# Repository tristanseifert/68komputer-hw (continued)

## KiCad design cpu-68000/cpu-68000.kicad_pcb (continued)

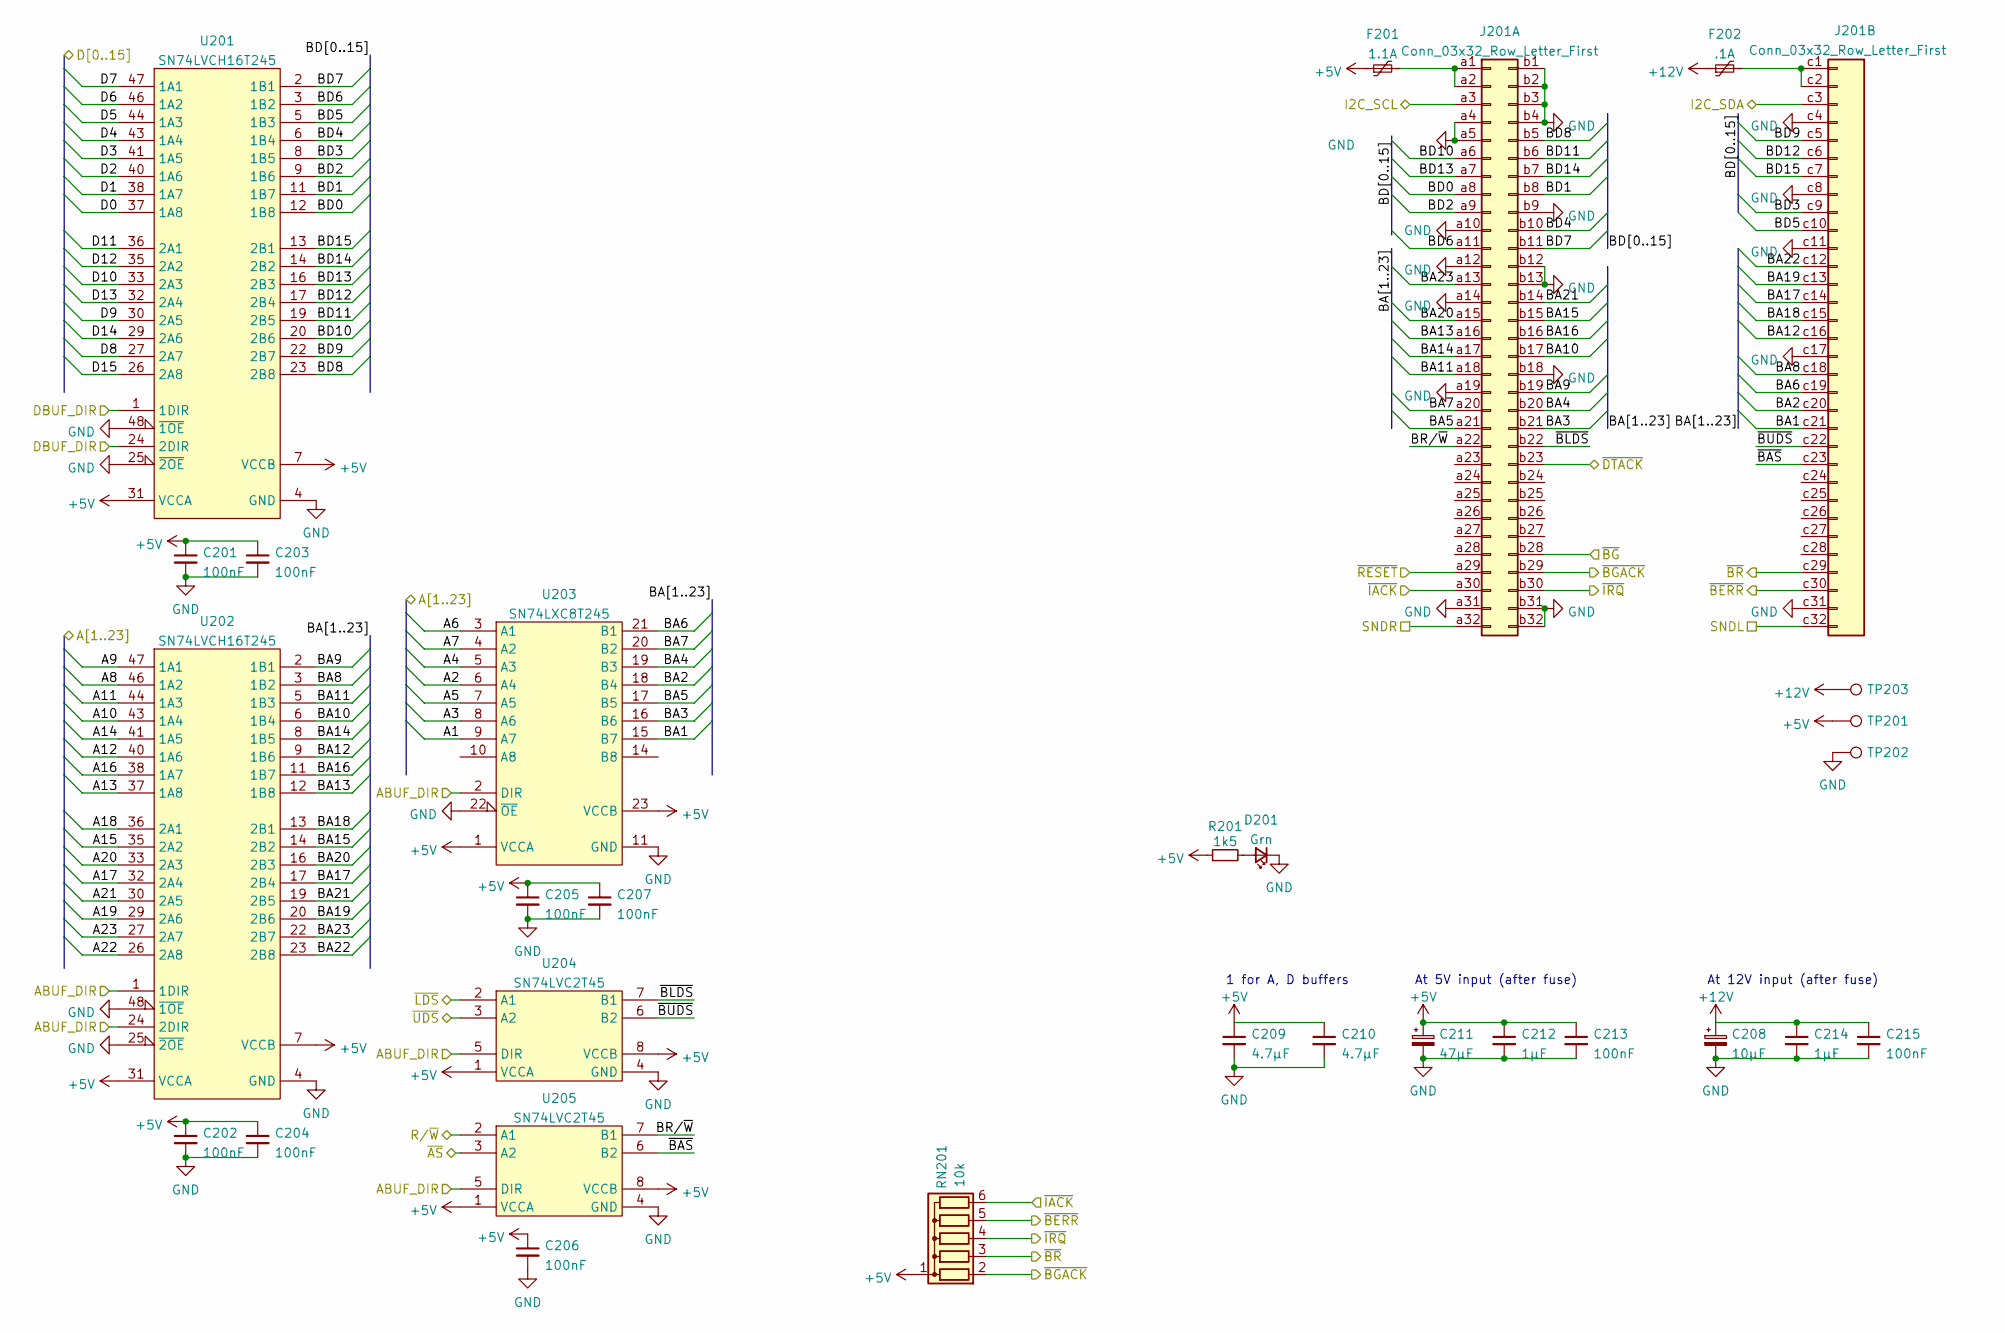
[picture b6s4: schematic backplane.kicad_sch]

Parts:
C201, C202, C203, C204, C205, C206, C207, C213, C215: 100nF; C_0805_2012Metric
C208: 10µF; CP_EIA-3528-21_Kemet-B; MPN TAJB106K025SNJ
C209, C210: 4.7µF; C_0805_2012Metric
C211: 47µF; CP_Radial_D6.3mm_P2.50mm; MPN A750EK476M1EAAE040
C212, C214: 1µF; C_0805_2012Metric
D201: Grn; H100Cxx; MPN H100CGD
F201: 1.1A; Fuse_Bourns_MF-SM_7.98x5.44mm; MPN MF-SM100/33-2
F202: .1A; Fuse_Littelfuse-NANO2-451_453; MPN NANOSMDC010F-2
J201: Conn_03x32_Row_Letter_First; DIN41612_R_3x32_Male_Horizontal_THT
R201: 1k5; R_0805_2012Metric
RN201: 10k; R_Array_SIP6; MPN 4606X-101-103LF
TP201, TP203: TestPoint; TestPoint_Loop_D2.60mm_Drill1.4mm_Beaded; MPN 534-5000
TP202: TestPoint; TestPoint_Loop_D2.60mm_Drill1.4mm_Beaded; MPN 534-5001
U201, U202: SN74LVCH16T245; TSSOP-48_6.1x12.5mm_P0.5mm
U203: SN74LXC8T245; TSSOP-24_4.4x7.8mm_P0.65mm
U204, U205: SN74LVC2T45; VSSOP-8_2.3x2mm_P0.5mm

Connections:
+5V: C201.1, C202.1, C203.1, C204.1, C205.1, C206.1, C207.1, C209.1, C210.1, C211.1, C212.1, C213.1, F201.1, R201.1, RN201.1 (common), TP201.1, U201.7 (VCCB), U201.18 (VCCB), U201.31 (VCCA), U201.42 (VCCA), U202.7 (VCCB), U202.18 (VCCB), U202.31 (VCCA), U202.42 (VCCA), U203.1 (VCCA), U203.23 (VCCB), U203.24 (VCCB), U204.1 (VCCA), U204.8 (VCCB), U205.1 (VCCA), U205.8 (VCCB); also elsewhere on the board
+12V: C208.1, C214.1, C215.1, F202.1, TP203.1; also elsewhere on the board
/A1: U203.9 (A7); also elsewhere on the board
/A2: U203.6 (A4); also elsewhere on the board
/A3: U203.8 (A6); also elsewhere on the board
/A4: U203.5 (A3); also elsewhere on the board
/A5: U203.7 (A5); also elsewhere on the board
/A6: U203.3 (A1); also elsewhere on the board
/A7: U203.4 (A2); also elsewhere on the board
/A8: U202.46 (1A2); also elsewhere on the board
/A9: U202.47 (1A1); also elsewhere on the board
/A10: U202.43 (1A4); also elsewhere on the board
/A11: U202.44 (1A3); also elsewhere on the board
/A12: U202.40 (1A6); also elsewhere on the board
/A13: U202.37 (1A8); also elsewhere on the board
/A14: U202.41 (1A5); also elsewhere on the board
/A15: U202.35 (2A2); also elsewhere on the board
/A16: U202.38 (1A7); also elsewhere on the board
/A17: U202.32 (2A4); also elsewhere on the board
/A18: U202.36 (2A1); also elsewhere on the board
/A19: U202.29 (2A6); also elsewhere on the board
/A20: U202.33 (2A3); also elsewhere on the board
/A21: U202.30 (2A5); also elsewhere on the board
/A22: U202.26 (2A8); also elsewhere on the board
/A23: U202.27 (2A7); also elsewhere on the board
/ABUF_DIR: U202.1 (1DIR), U202.24 (2DIR), U203.2 (DIR), U204.5 (DIR), U205.5 (DIR); also elsewhere on the board
/Backplane Connection/BA1: J201.c21, U203.15 (B7)
/Backplane Connection/BA2: J201.c20, U203.18 (B4)
/Backplane Connection/BA3: J201.b21, U203.16 (B6)
/Backplane Connection/BA4: J201.b20, U203.19 (B3)
/Backplane Connection/BA5: J201.a21, U203.17 (B5)
/Backplane Connection/BA6: J201.c19, U203.21 (B1)
/Backplane Connection/BA7: J201.a20, U203.20 (B2)
/Backplane Connection/BA8: J201.c18, U202.3 (1B2)
/Backplane Connection/BA9: J201.b19, U202.2 (1B1)
/Backplane Connection/BA10: J201.b17, U202.6 (1B4)
/Backplane Connection/BA11: J201.a18, U202.5 (1B3)
/Backplane Connection/BA12: J201.c16, U202.9 (1B6)
/Backplane Connection/BA13: J201.a16, U202.12 (1B8)
/Backplane Connection/BA14: J201.a17, U202.8 (1B5)
/Backplane Connection/BA15: J201.b15, U202.14 (2B2)
/Backplane Connection/BA16: J201.b16, U202.11 (1B7)
/Backplane Connection/BA17: J201.c14, U202.17 (2B4)
/Backplane Connection/BA18: J201.c15, U202.13 (2B1)
/Backplane Connection/BA19: J201.c13, U202.20 (2B6)
/Backplane Connection/BA20: J201.a15, U202.16 (2B3)
/Backplane Connection/BA21: J201.b14, U202.19 (2B5)
/Backplane Connection/BA22: J201.c12, U202.23 (2B8)
/Backplane Connection/BA23: J201.a13, U202.22 (2B7)
/Backplane Connection/BD0: J201.a8, U201.12 (1B8)
/Backplane Connection/BD1: J201.b8, U201.11 (1B7)
/Backplane Connection/BD2: J201.a9, U201.9 (1B6)
/Backplane Connection/BD3: J201.c9, U201.8 (1B5)
/Backplane Connection/BD4: J201.b10, U201.6 (1B4)
/Backplane Connection/BD5: J201.c10, U201.5 (1B3)
/Backplane Connection/BD6: J201.a11, U201.3 (1B2)
/Backplane Connection/BD7: J201.b11, U201.2 (1B1)
/Backplane Connection/BD8: J201.b5, U201.23 (2B8)
/Backplane Connection/BD9: J201.c5, U201.22 (2B7)
/Backplane Connection/BD10: J201.a6, U201.20 (2B6)
/Backplane Connection/BD11: J201.b6, U201.19 (2B5)
/Backplane Connection/BD12: J201.c6, U201.17 (2B4)
/Backplane Connection/BD13: J201.a7, U201.16 (2B3)
/Backplane Connection/BD14: J201.b7, U201.14 (2B2)
/Backplane Connection/BD15: J201.c7, U201.13 (2B1)
/Backplane Connection/BR/~W: J201.a22, U205.7 (B1)
/Backplane Connection/~BAS: J201.c23, U205.6 (B2)
/Backplane Connection/~BLDS: J201.b22, U204.7 (B1)
/Backplane Connection/~BUDS: J201.c22, U204.6 (B2)
/D0: U201.37 (1A8); also elsewhere on the board
/D1: U201.38 (1A7); also elsewhere on the board
/D2: U201.40 (1A6); also elsewhere on the board
/D3: U201.41 (1A5); also elsewhere on the board
/D4: U201.43 (1A4); also elsewhere on the board
/D5: U201.44 (1A3); also elsewhere on the board
/D6: U201.46 (1A2); also elsewhere on the board
/D7: U201.47 (1A1); also elsewhere on the board
/D8: U201.27 (2A7); also elsewhere on the board
/D9: U201.30 (2A5); also elsewhere on the board
/D10: U201.33 (2A3); also elsewhere on the board
/D11: U201.36 (2A1); also elsewhere on the board
/D12: U201.35 (2A2); also elsewhere on the board
/D13: U201.32 (2A4); also elsewhere on the board
/D14: U201.29 (2A6); also elsewhere on the board
/D15: U201.26 (2A8); also elsewhere on the board
/DBUF_DIR: U201.1 (1DIR), U201.24 (2DIR); also elsewhere on the board
/I2C_SCL: J201.a3; also elsewhere on the board
/I2C_SDA: J201.c3; also elsewhere on the board
/R/~W: U205.2 (A1); also elsewhere on the board
/SNDL: J201.c32
/SNDR: J201.a32
/~AS: U205.3 (A2); also elsewhere on the board
/~BGACK: J201.b29, RN201.2 (R1); also elsewhere on the board
/~BG: J201.b28; also elsewhere on the board
/~BR: J201.c29, RN201.3 (R2); also elsewhere on the board
/~DTACK: J201.b23; also elsewhere on the board
/~EXT_BERR: J201.c30, RN201.5 (R4); also elsewhere on the board
/~IACK_EXT: J201.a30, RN201.6 (R5); also elsewhere on the board
/~IRQ_EXT: J201.b30, RN201.4 (R3); also elsewhere on the board
/~LDS: U204.2 (A1); also elsewhere on the board
/~RESET: J201.a29; also elsewhere on the board
/~UDS: U204.3 (A2); also elsewhere on the board
GND: C201.2, C202.2, C203.2, C204.2, C205.2, C206.2, C207.2, C208.2, C209.2, C210.2, C211.2, C212.2, C213.2, C214.2, C215.2, D201.1 (K), J201.a4, J201.a5, J201.a10, J201.a12, J201.a14, J201.a19, J201.a31, J201.b1, J201.b2, J201.b3, J201.b4, J201.b9, J201.b12, J201.b13, J201.b18, J201.b31, J201.b32, J201.c4, J201.c8, J201.c11, J201.c17, J201.c31, TP202.1, U201.4 (GND), U201.10 (GND), U201.15 (GND), U201.21 (GND), U201.25 (~2OE), U201.28 (GND), U201.34 (GND), U201.39 (GND), U201.45 (GND), U201.48 (~1OE), U202.4 (GND), U202.10 (GND), U202.15 (GND), U202.21 (GND), U202.25 (~2OE), U202.28 (GND), U202.34 (GND), U202.39 (GND), U202.45 (GND), U202.48 (~1OE), U203.11 (GND), U203.12 (GND), U203.13 (GND), U203.22 (~OE), U204.4 (GND), U205.4 (GND); also elsewhere on the board
unnamed: D201.2 (A), R201.2
unnamed: F201.2, J201.a1, J201.a2
unnamed: F202.2, J201.c1, J201.c2

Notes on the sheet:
At 5V input (after fuse)
1 for A, D buffers
At 12V input (after fuse)

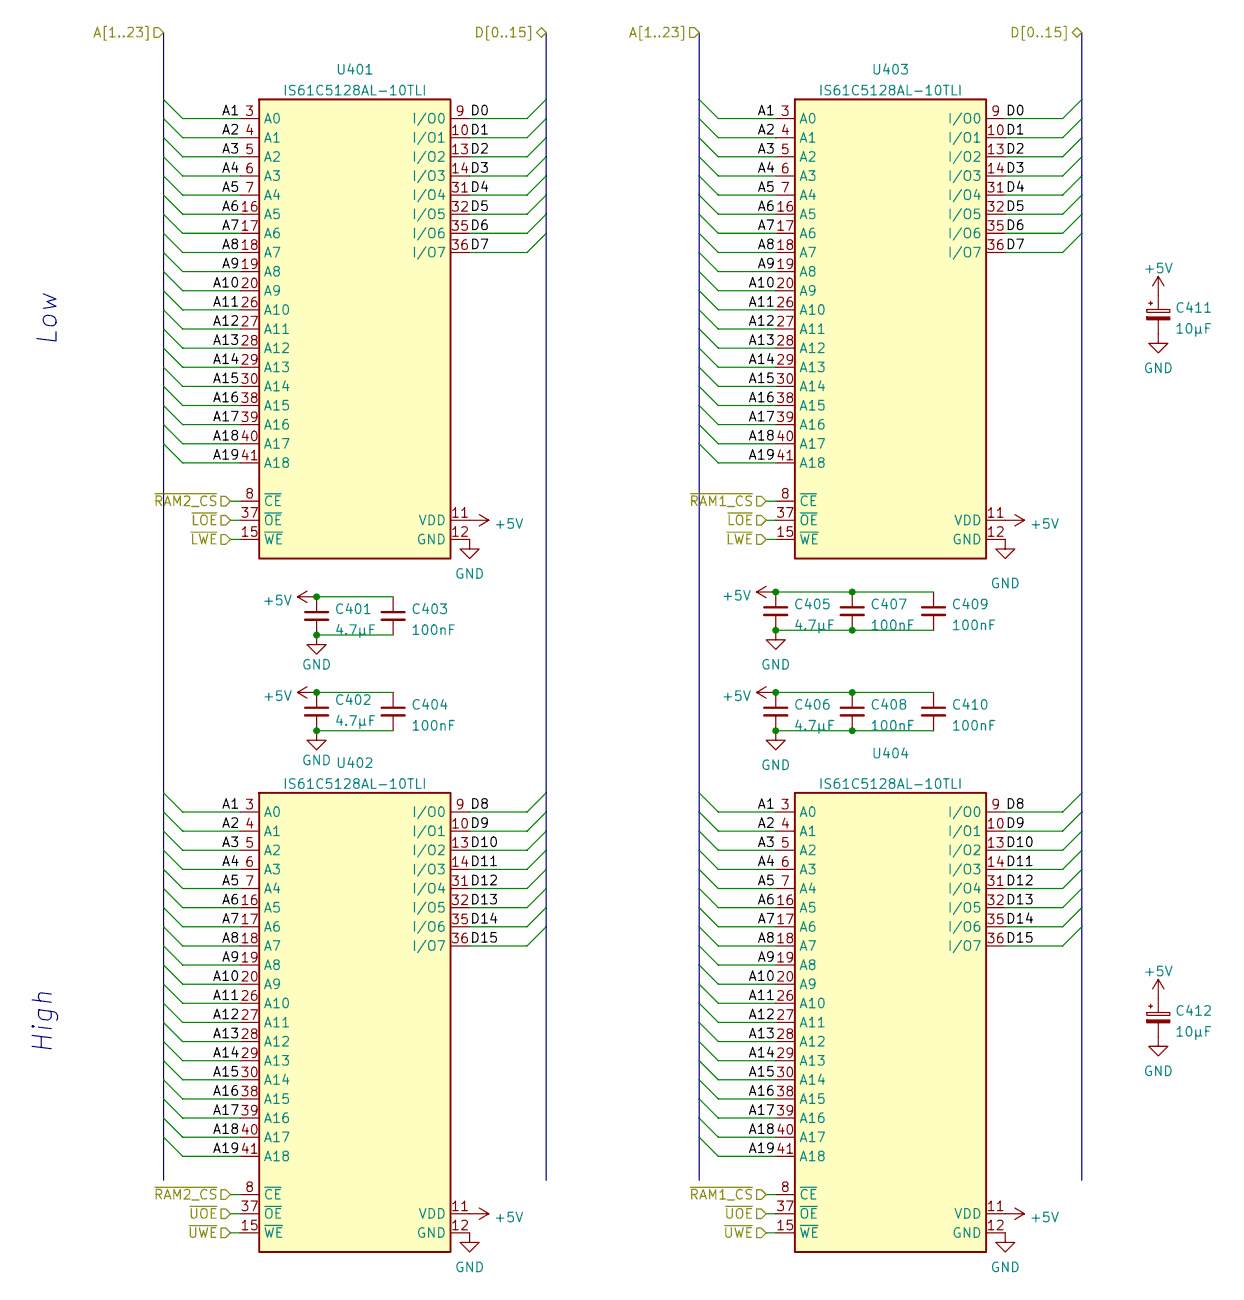
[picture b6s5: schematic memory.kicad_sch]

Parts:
C401, C402, C405, C406: 4.7µF; C_0805_2012Metric
C403, C404, C407, C408, C409, C410: 100nF; C_0805_2012Metric
C411, C412: 10µF; CP_EIA-3216-18_Kemet-A
U401, U402, U403, U404: IS61C5128AL-10TLI; TSOP-II-44_10.16x18.41mm_P0.8mm

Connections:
+5V: C401.1, C402.1, C403.1, C404.1, C405.1, C406.1, C407.1, C408.1, C409.1, C410.1, C411.1, C412.1, U401.11 (VDD), U401.33 (VDD), U402.11 (VDD), U402.33 (VDD), U403.11 (VDD), U403.33 (VDD), U404.11 (VDD), U404.33 (VDD); also elsewhere on the board
/A1: U401.3 (A0), U402.3 (A0), U403.3 (A0), U404.3 (A0); also elsewhere on the board
/A2: U401.4 (A1), U402.4 (A1), U403.4 (A1), U404.4 (A1); also elsewhere on the board
/A3: U401.5 (A2), U402.5 (A2), U403.5 (A2), U404.5 (A2); also elsewhere on the board
/A4: U401.6 (A3), U402.6 (A3), U403.6 (A3), U404.6 (A3); also elsewhere on the board
/A5: U401.7 (A4), U402.7 (A4), U403.7 (A4), U404.7 (A4); also elsewhere on the board
/A6: U401.16 (A5), U402.16 (A5), U403.16 (A5), U404.16 (A5); also elsewhere on the board
/A7: U401.17 (A6), U402.17 (A6), U403.17 (A6), U404.17 (A6); also elsewhere on the board
/A8: U401.18 (A7), U402.18 (A7), U403.18 (A7), U404.18 (A7); also elsewhere on the board
/A9: U401.19 (A8), U402.19 (A8), U403.19 (A8), U404.19 (A8); also elsewhere on the board
/A10: U401.20 (A9), U402.20 (A9), U403.20 (A9), U404.20 (A9); also elsewhere on the board
/A11: U401.26 (A10), U402.26 (A10), U403.26 (A10), U404.26 (A10); also elsewhere on the board
/A12: U401.27 (A11), U402.27 (A11), U403.27 (A11), U404.27 (A11); also elsewhere on the board
/A13: U401.28 (A12), U402.28 (A12), U403.28 (A12), U404.28 (A12); also elsewhere on the board
/A14: U401.29 (A13), U402.29 (A13), U403.29 (A13), U404.29 (A13); also elsewhere on the board
/A15: U401.30 (A14), U402.30 (A14), U403.30 (A14), U404.30 (A14); also elsewhere on the board
/A16: U401.38 (A15), U402.38 (A15), U403.38 (A15), U404.38 (A15); also elsewhere on the board
/A17: U401.39 (A16), U402.39 (A16), U403.39 (A16), U404.39 (A16); also elsewhere on the board
/A18: U401.40 (A17), U402.40 (A17), U403.40 (A17), U404.40 (A17); also elsewhere on the board
/A19: U401.41 (A18), U402.41 (A18), U403.41 (A18), U404.41 (A18); also elsewhere on the board
/D0: U401.9 (I/O0), U403.9 (I/O0); also elsewhere on the board
/D1: U401.10 (I/O1), U403.10 (I/O1); also elsewhere on the board
/D2: U401.13 (I/O2), U403.13 (I/O2); also elsewhere on the board
/D3: U401.14 (I/O3), U403.14 (I/O3); also elsewhere on the board
/D4: U401.31 (I/O4), U403.31 (I/O4); also elsewhere on the board
/D5: U401.32 (I/O5), U403.32 (I/O5); also elsewhere on the board
/D6: U401.35 (I/O6), U403.35 (I/O6); also elsewhere on the board
/D7: U401.36 (I/O7), U403.36 (I/O7); also elsewhere on the board
/D8: U402.9 (I/O0), U404.9 (I/O0); also elsewhere on the board
/D9: U402.10 (I/O1), U404.10 (I/O1); also elsewhere on the board
/D10: U402.13 (I/O2), U404.13 (I/O2); also elsewhere on the board
/D11: U402.14 (I/O3), U404.14 (I/O3); also elsewhere on the board
/D12: U402.31 (I/O4), U404.31 (I/O4); also elsewhere on the board
/D13: U402.32 (I/O5), U404.32 (I/O5); also elsewhere on the board
/D14: U402.35 (I/O6), U404.35 (I/O6); also elsewhere on the board
/D15: U402.36 (I/O7), U404.36 (I/O7); also elsewhere on the board
/~LOE: U401.37 (~OE), U403.37 (~OE); also elsewhere on the board
/~LWE: U401.15 (~WE), U403.15 (~WE); also elsewhere on the board
/~RAM1_CS: U403.8 (~CE), U404.8 (~CE); also elsewhere on the board
/~RAM2_CS: U401.8 (~CE), U402.8 (~CE); also elsewhere on the board
/~UOE: U402.37 (~OE), U404.37 (~OE); also elsewhere on the board
/~UWE: U402.15 (~WE), U404.15 (~WE); also elsewhere on the board
GND: C401.2, C402.2, C403.2, C404.2, C405.2, C406.2, C407.2, C408.2, C409.2, C410.2, C411.2, C412.2, U401.12 (GND), U401.34 (GND), U402.12 (GND), U402.34 (GND), U403.12 (GND), U403.34 (GND), U404.12 (GND), U404.34 (GND); also elsewhere on the board

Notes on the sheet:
Low
High

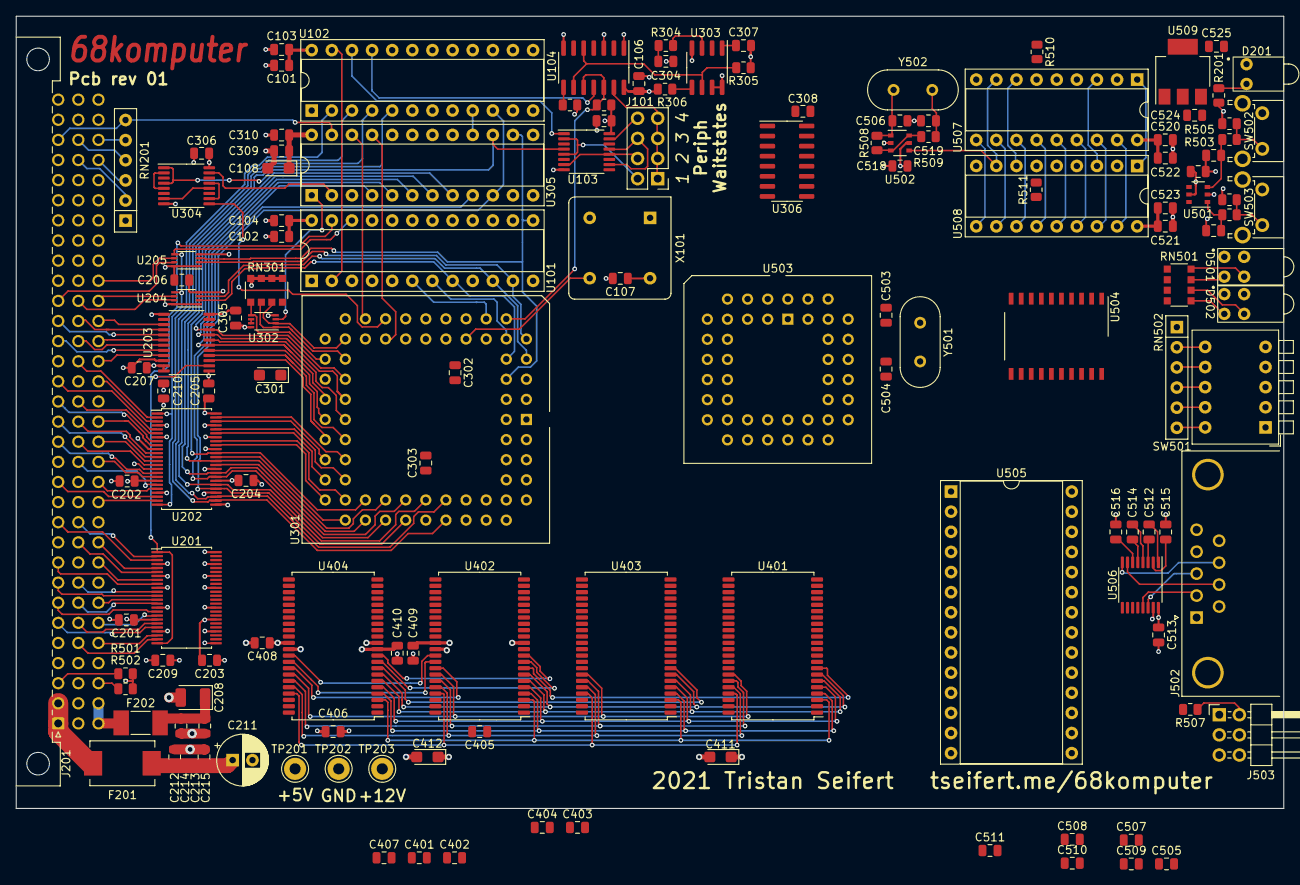
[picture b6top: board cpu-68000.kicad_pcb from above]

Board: 4 copper layers, 160.0 x 100.0 mm, 137 parts (0 on the bottom side), 197 nets.

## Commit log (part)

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2018-12-04 add readme
2018-12-04 added psram to 68010 board
2018-12-04 added address decoding, interrupt handling, external bus interface
2018-12-07 added 68681 DUART
2018-12-07 routed address/data between banks of RAM/ROM
2018-12-08 added TIL311, DLx2416 LED displays
2018-12-10 added SIMM socket footprint
2018-12-12 routed more signals, added power connector
2019-09-28 more stuff got routed for 68008
2019-09-29 routed duart IO and serial channels
2019-09-30 finish routng
2019-10-06 replaced CPLD with PLDs
2019-10-08 added uart/rs232 adapter
2019-10-13 rev 01 boards for cpu-68008 sent to fab
2019-10-25 preliminary expansion backplane for 68komputer-008
2019-10-27 finished routing backplane
2019-10-28 start work on sound board
2019-10-29 start working on adding midi in/out to sound board
2019-10-31 finished midi circuit frontends
2019-11-04 Added 8-bit IDE board Finished routing of sound board
2019-11-06 finished schematic for tms9918 board, started routing
2019-11-15 basic 68000 based computer
2019-11-16 Finished routing expansion connector for 68000 board
2019-11-17 Started working on 2MB RAM expansion board for 68000 CPU
2019-11-18 2MB RAM Expansion: - Finished routing all signals
2019-11-21 IO board: - Added 82C55 PIO
    RAM board:
    - Tweaked tolerances between some traces
    - Fixed naming of parts
2020-02-11 Started work on sound board
2021-10-28 moved old files
2021-11-04 added memory, peripherals
2021-11-11 Peripherals and general connection stuff
2021-11-12 More backplane stuff; added footprints for most
2021-11-13 Placed most items on pcb
    - Laid out most components where they should go on the board; mostly
    routed the connector side of the bus buffers and the address bus
    - Added 3d models for PLCC sockets, RTC clock module
2021-11-14 More control signals; start RAM routing
    - Started routing the address/data bus for the RAM, including some
    rejigging of the data bus layout
    - Added a fuse and power conditioning for 12V, to be used for the analog
    section on the sound side
2021-11-15 Start peripheral routing
    - Begin routing some of the peripheral section, particularly the NVRAM
    is fully connected (sans chip select) now
    - Added an I2C EEPROM (with serial number) on board the CPU card for
    automatic identification
    - Minor cleanups and space squishing of the board. There may in fact be
    sufficient space to still fit a boot ROM (likely a surface mount
2021-11-16 Completed board routing
    - Finished routing all of the signals on the board :D it still needs a
    check over to make sure it's not fucked though
    - Split sound stuff into its own sheet
2021-11-17 Added memory access type signal
    - Since function codes aren't provided on the backplane, we instead have
    a signal that's driven low to indicate that the access is to memory
    rather than some other type (CPU space). It's open drain with a 10k
    pullup, which is _hopefully_ sufficient.
2021-11-19 Begin work on blinkenlights board
    - This is a simple board with pretty TIL311 displays for the
    address/data busses, lots of blinking lights, and sockets for boot
    ROMs for testing. It connects directly to the CPU board through a
    female right angle DIN41612 connector.
    - Added footprints for Deltron 571-0x00 test sockets
2021-11-30 Tweaks to IOs on 68k board
    - Added an I2C IRQ line, so that I2C peripherals can request servicing.
    This is mostly used for the control panel/backplane management
    functions.
2021-12-01 Switched one of the RAMs for a flash chip
    - This should allow us to have a boot ROM on the board; it will need to
    be bootstraped and programmed in-system by some external jig though.
2021-12-01 Added high byte flash chip
    - Replaced one of the RAMs with another flash, so that we can have
    on-board boot ROM of 1M. It'll have to be programmed in system (or
    very flimsily out of system before soldering) so a switch to remap the
    flash to elsehwere in the address space is provided (formerly BERR
    inhibit switch)
2021-12-01 Added ROM sockets to blinkenlights
    - Also started routing some of the IOs and powers for the displays
2021-12-03 did some things
2021-12-05 Added ATSAM4 CPU to blinkenlights
    - This big ol ARM chip is gonna be hooked up to the 68k bus, so that we
    can do bus transactions and (slowly) single step the physical machine.
    This will make bringup simpler and allow programming of the flash
    chips on the CPU board.
    - Added a footprint for an USB-C connector (lol)
2021-12-06 Routed address/data bus on blinkenlights
    - It goes to the funky hex display bois now and is routed so that it
    should be pretty ez to yeet on down into level shifters for the big
    ARM chip that runs the show
2021-12-07 Connected data/address bus to expanders
    - Finished routing the remaining address and data lines to the SPI IO
    expanders, which are used externally to control the bus. Also removed
    some superfluous level shifters
2021-12-08 Mostly finished blinkenlights contraption
    - Added some headers that can have logic probes connected to them; we
    need to route them and ensure the pins are correct
2021-12-09 Expose CPU function code on backplane
    - Routed the function code signals to the backplane; they're pulled to
    ground so that if a bus mastering device doesn't drive them the world
    won't explode (it will be a supervisor data access)
2021-12-09 Added a few more test points
    - Also, tweaked the package of the I2C translator to be one that's
    actually in stock
2021-12-11 Minor cleanup of CPU board
    - Switched out of stock 2 bit level shifters for 8 bit part we already
    have; this means that the function codes will be buffered along with
    all other signals.
2021-12-12 Replaced many B case caps with A case
    - There were sufficiently many 5V tantalum capcaitors on the
    blinkenlights board with the B case footprint (for 25V) rather than
    the A case (for 16V) assigned.
2021-12-14 Added logic equations for CPU board
    - These are the equations that get programmed into the GALs that
    actually drive the control signals and so forth.
    - Minor cleanups to the CPU board
2021-12-16 More minor tweaks to CPU board
    - Added an I2C expansion header, which some GPIO stuff could be
    connected to for testing, and to probe the on-board I2C bus with an
    external logic analyzer.
    - The parts on it are frozen at this point since they have been ordered
2021-12-16 Added gerbers sent to manufacturing (Rev 01)
2021-12-30 Minor fixes for wrong parts
    - Mostly an incorrect fuse value and the wrong type of buffer on the CPU
    board buttons
2021-12-31 Finished routing new address/data from backplane
    - Routed the traces for the address/data bus from the connector and
    along the memories that need them. The NVRAM is fully connected to the
    bus, along with the peripheral section.
    We'll need to assign address lines to the SRAMs, then connect the
    flash chips next.
2022-01-02 More footprints and symbols
    - Created footprints/symbols for a few power regulation components for
    the backplane management board
2022-01-02 Routed backplane mgmt board
    - Finished routing of the complete backplane management board; it
    doesn't do much other than provide power (with monitoring) and an
    audio output (with volume control) from the backplane.
    Originally this was gonna have a display but there's no space on the
    front panel for that.
2022-01-04 More backplane work
    - Added pull up/down resistors at end of board to bring the various
    data/address lines to a controlled state, rather than floating, and
    attempt to control reflections
    - Added a clock buffer so each slot gets its own nice buffered clock.
    The clock buffer used is only 1:5 fanout, so the last two slots share
    a clock line.
2022-01-05 More optimization of backplane
    - Fixed a few DRC errors and added LEDs with the spare IOs on the I2C
    expander.
2022-01-08 Start work on a relay output board
    - This is a super simple test peripheral board, just a latch and a bunch
    of relays for clicky sounds. It serves as a test of the backplane and
    I2C based detection/address allocation mechanisms.
2022-01-08 Function codes, /DTACK for relay board
    - Consider the state of the function code signals (so we don't decode
    CPU space cycles as accesses) and assert /DTACK when the latch signal
    is asserted. This should work for bus speeds of up to around 16MHz
2022-01-10 Minor tweaks to all boards
    - Moved around some traces on the 68000 CPU card for prettiness
    - Added a connector on the backplane to provide +5V/+12V without a
    management card installed (for testing)
2022-01-12 Tweaks to CPU board layout
    - Made some more space around the ROM sockets, in hopes of maybe fitting
    spicier sockets than standard machine pin sockets. There's the Aries
    Electronics EJECT-A-DIP sockets that might fit now.
2022-01-14 Minor tweaks to power board
    - Reorganized the layout of input protection to accomodate a different
    (cheaper) input connector; also added some better thermal dissipation
    for the protection MOSFETs.
2022-01-14 Removed GAL from relay board
    - Replaced the GAL on the relay board with some hard 74-series logic;
    this means the board needs zero "hard to get" parts.
    All the address decoding is done by a '688 magnitude comparison IC,
    which is LS logic so this board needs to consist of HCT logic to deal
    with its lower active high level.
    - Replaced 3D model for the hexadecimal rotary switches to one that has
2022-01-24 Added +12V regulator to backplane mgmt
    - Added the components for a discrete switching regulator (that is, with
    external switching MOSFETs, but a fancy little switching controller)
    to generate the 12V rail, at up to 10A. This is then further regulated
    to provide 5V for the board itself, and for the rest of the system.
2022-02-03 Minor layout tweaks across the board
    - Added an input for a test clock, and a jumper for sending this clock
    instead of the CPU clock to the clock pins of the expansion cards on
    the backplane boards
    - Reworked a bunch of the power supply board
    - Minor changes (to consolidate BOMs) on CPU board for some capacitors,
    they were replaced with SMD versions
2022-02-05 Finished backplane breakout
    - All of the backplane signals (for an expansion card) are brought out
    to 2x10 headers, which can connect to the logic analyzer through
    isolation adapters or direct probing in a more compact pinout
    - Added a footprint for a shrouded 2x10 header
2022-03-02 Added backplane GAL equations
